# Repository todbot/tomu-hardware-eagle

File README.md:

# tomu-hardware-eagle

My attempt at translating the wonderful [im-tomu/tomu-hardware](https://github.com/im-tomu/tomu-hardware) project ([crowdfunding now on CrowdSupply!](https://www.crowdsupply.com/sutajio-kosagi/tomu/)) from Kicad into Eagle.

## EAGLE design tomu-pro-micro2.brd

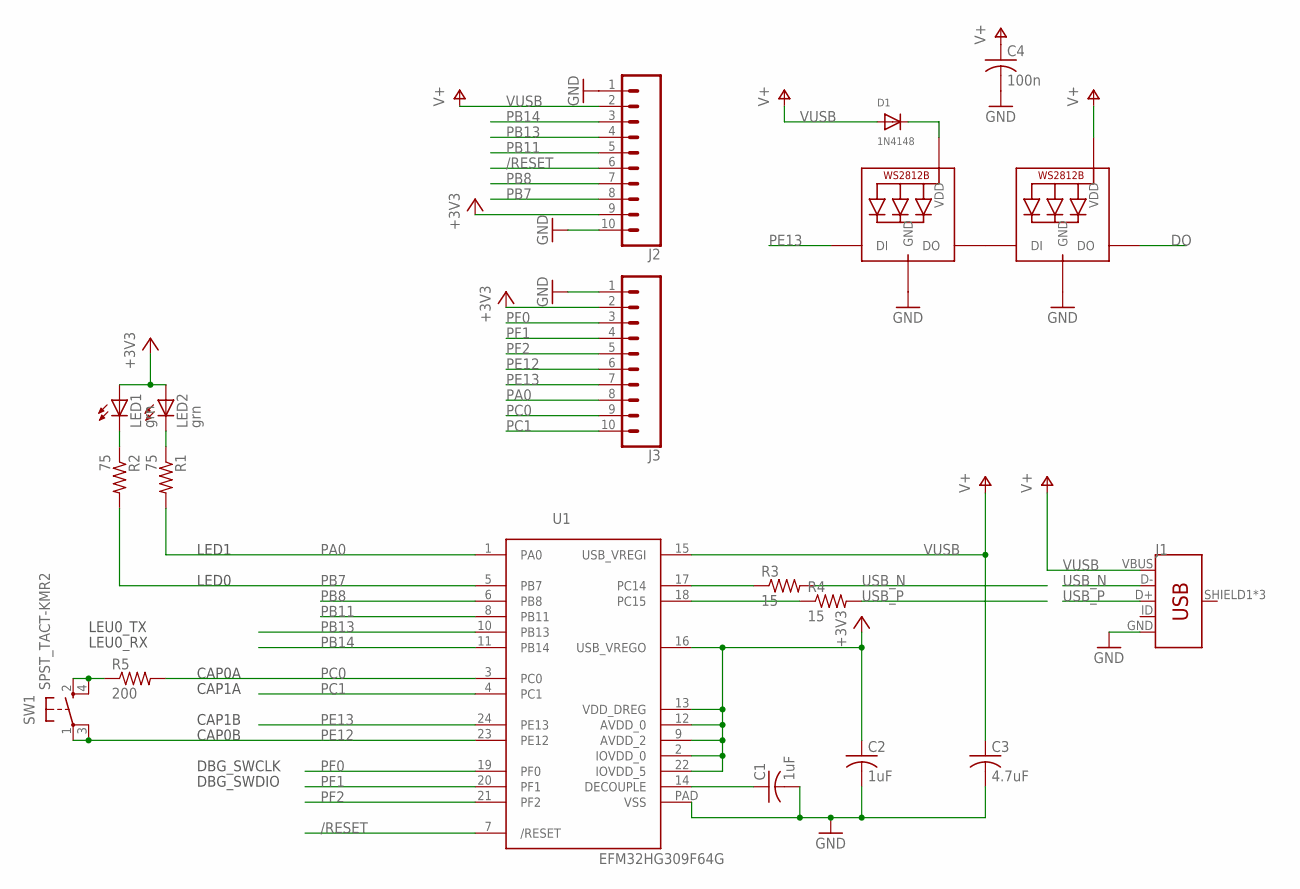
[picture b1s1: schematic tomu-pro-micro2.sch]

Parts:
C1, C2: 1uF; C0603
C3: 4.7uF; C0603
C4: 100n; C0603
D1: 1N4148; SOD-323F
J1: USB_MICRO-B_FEMALE-SMT; USB-B-MICRO-SMD
J2, J3: CONN_10"; 1X10
L1, L2: WS2812B3535; LED3535
LED1, LED2: grn; CHIP-LED0603
R1, R2: 75; R0603
R3, R4: 15; R0603
R5: 200; R0603
SW1: SPST_TACT-KMR2; KMR2
U1: EFM32HG309F64G; QFN24PAD

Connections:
+3V3: C2.1, J2.9, J3.2, LED1.A, LED2.A, U1.2 (IOVDD_0), U1.9 (AVDD_2), U1.12 (AVDD_0), U1.13 (VDD_DREG), U1.16 (USB_VREGO), U1.22 (IOVDD_5)
/RESET: J2.6, U1.7 (/RESET)
DECOUPLE: C1.1, U1.14 (DECOUPLE)
DO: L2.3 (DO)
GND: C1.2, C2.2, C3.2, C4.2, J1.GND, J2.1, J2.10, J3.1, L1.4 (GND), L2.4 (GND), U1.PAD (VSS)
unnamed: L1.3 (DO), L2.1 (DI)
unnamed: D1.C, L1.2 (VDD)
unnamed: LED1.C, R2.1
unnamed: LED2.C, R1.1
unnamed: R5.1, SW1.2 (S), SW1.4 (S1)
PA0: J3.8, R1.2, U1.1 (PA0)
PB7: J2.8, R2.2, U1.5 (PB7)
PB8: J2.7, U1.6 (PB8)
PB11: J2.5, U1.8 (PB11)
PB13: J2.4, U1.10 (PB13)
PB14: J2.3, U1.11 (PB14)
PC0: J3.9, R5.2, U1.3 (PC0)
PC1: J3.10, U1.4 (PC1)
PE12: J3.6, SW1.1, SW1.3 (P1), U1.23 (PE12)
PE13: J3.7, L1.1 (DI), U1.24 (PE13)
PF0: J3.3, U1.19 (PF0)
PF1: J3.4, U1.20 (PF1)
PF2: J3.5, U1.21 (PF2)
RUSB_N: R3.1, U1.17 (PC14)
RUSB_P: R4.1, U1.18 (PC15)
USB_N: J1.D-, R3.2
USB_P: J1.D+, R4.2
VUSB: C3.1, C4.1, D1.A, J1.VBUS, J2.2, L2.2 (VDD), U1.15 (USB_VREGI)

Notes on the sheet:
LED1
LED0
DBG_SWCLK
DBG_SWDIO
LEU0_TX
LEU0_RX
CAP0A
CAP1A
CAP1B
CAP0B

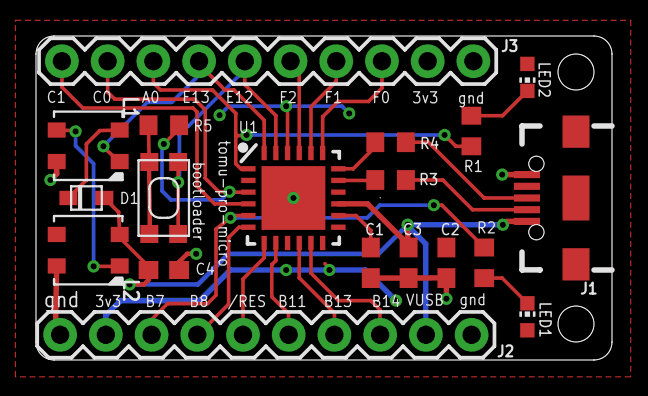
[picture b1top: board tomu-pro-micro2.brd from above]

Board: 2 copper layers, 32.0 x 18.0 mm, 19 parts (0 on the bottom side), 27 nets.

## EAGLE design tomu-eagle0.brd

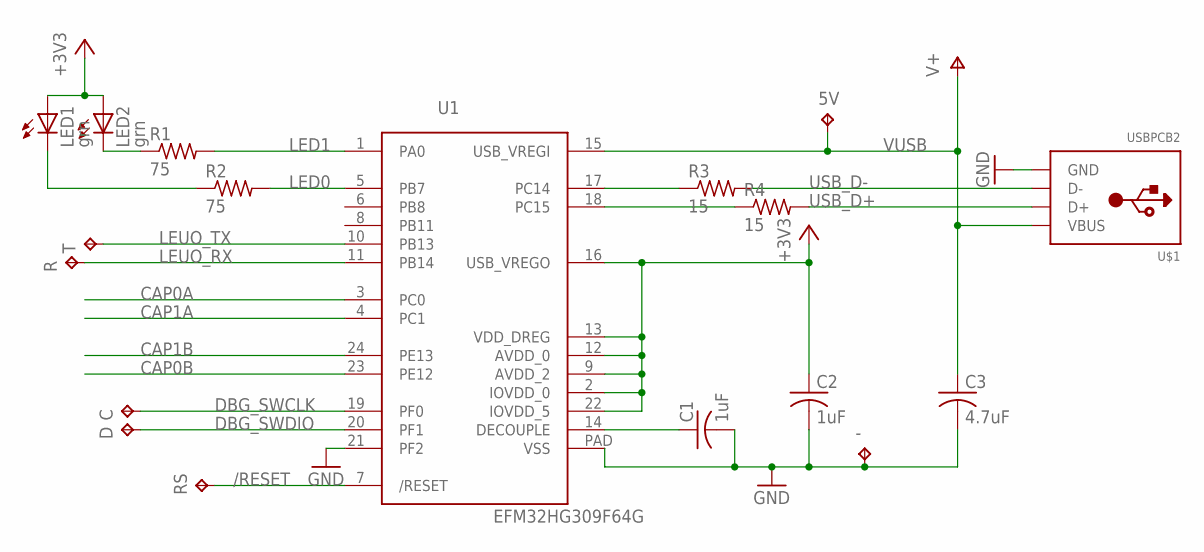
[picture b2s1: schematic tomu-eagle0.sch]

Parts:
5V: TPTP10R; TP10R
-: TPTP10SQ; TP10SQ
C: TPTP10R; TP10R
C1, C2: 1uF; C0402K
C3: 4.7uF; C0402K
D: TPTP10R; TP10R
LED1, LED2: grn; CHIP-LED0603
R: TPTP10R; TP10R
R1, R2: 75; R0402
R3, R4: 15; R0402
RS: TPTP10R; TP10R
T: TPTP10R; TP10R
U1: EFM32HG309F64G; QFN24PAD
U$1: USBPCB2; USB-A-PCB-2

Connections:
+3V3: C2.1, LED1.A, LED2.A, U1.2 (IOVDD_0), U1.9 (AVDD_2), U1.12 (AVDD_0), U1.13 (VDD_DREG), U1.16 (USB_VREGO), U1.22 (IOVDD_5)
/RESET: RS.TP, U1.7 (/RESET)
CAP0A: U1.3 (PC0)
CAP0B: U1.23 (PE12)
CAP1A: U1.4 (PC1)
CAP1B: U1.24 (PE13)
DBG_SWCLK: C.TP, U1.19 (PF0)
DBG_SWDIO: D.TP, U1.20 (PF1)
DECOUPLE: C1.1, U1.14 (DECOUPLE)
GND: -.TP, C1.2, C2.2, C3.2, U1.21 (PF2), U1.PAD (VSS), U$1.GND
LED0: R2.2, U1.5 (PB7)
LED1: R1.2, U1.1 (PA0)
LEUO_RX: R.TP, U1.11 (PB14)
LEUO_TX: T.TP, U1.10 (PB13)
unnamed: LED1.C, R2.1
unnamed: LED2.C, R1.1
RUSB_D+: R4.1, U1.18 (PC15)
RUSB_D-: R3.1, U1.17 (PC14)
USB_D+: R4.2, U$1.USB_P (D+)
USB_D-: R3.2, U$1.USB_M (D-)
VUSB: 5V.TP, C3.1, U1.15 (USB_VREGI), U$1.5V (VBUS)

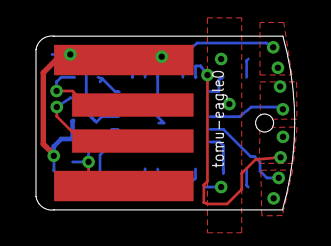
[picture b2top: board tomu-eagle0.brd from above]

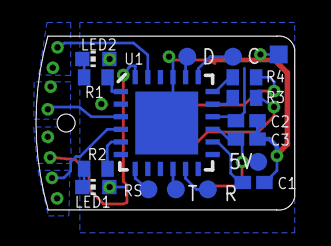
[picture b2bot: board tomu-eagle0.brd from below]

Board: 2 copper layers, 14.4 x 9.7 mm, 18 parts (17 on the bottom side), 17 nets.

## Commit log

2018-01-26 added first pass at touch sensors
2018-01-26 fixed up touch sensor
2018-01-26 minor cleanup
2018-01-26 sigh. QFN24 is 5x5 not 4x4
2018-01-26 still dealing with QFN 4x4 -> 5x5 issues
2018-01-26 fix CAP1A/CAP1B positions
2018-01-27 added first pass at "easy" version
2018-01-28 more fixes
2018-01-28 added screenshot
2018-01-28 added sch img
2018-01-28 fix images
2018-01-28 resize sch
2018-01-28 add sch
2018-02-01 added tomu-eagle1, more faithful to original tomu 0.4
2018-02-01 fixes to tomu-eagle1
2018-02-01 more fixes to tomu-eagle1
2018-02-01 more fixes, update readme
2018-02-10 small updates to tomu-eagle-easy
2018-02-10 added tomu-eagle-easy pic
2018-03-27 added tomo-pro-micro breakout board
2018-04-06 added tomu-pro-micro docs
2018-04-06 LED resistors should be 75 not 15 (or maybe 52 as in the tomu bom)
2018-05-20 added tomu-pro-micro1 board
2018-05-22 fix EFM32HG309 QFN pad spacing issue. omg what a slog
2018-05-28 fix problems with tomo-pro-micro1

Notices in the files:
parts and their libraries:
SparkFun-Connectors: Licensing: Creative Commons ShareAlike 4.0 International - https://creativecommons.org/licenses/by-sa/4.0
